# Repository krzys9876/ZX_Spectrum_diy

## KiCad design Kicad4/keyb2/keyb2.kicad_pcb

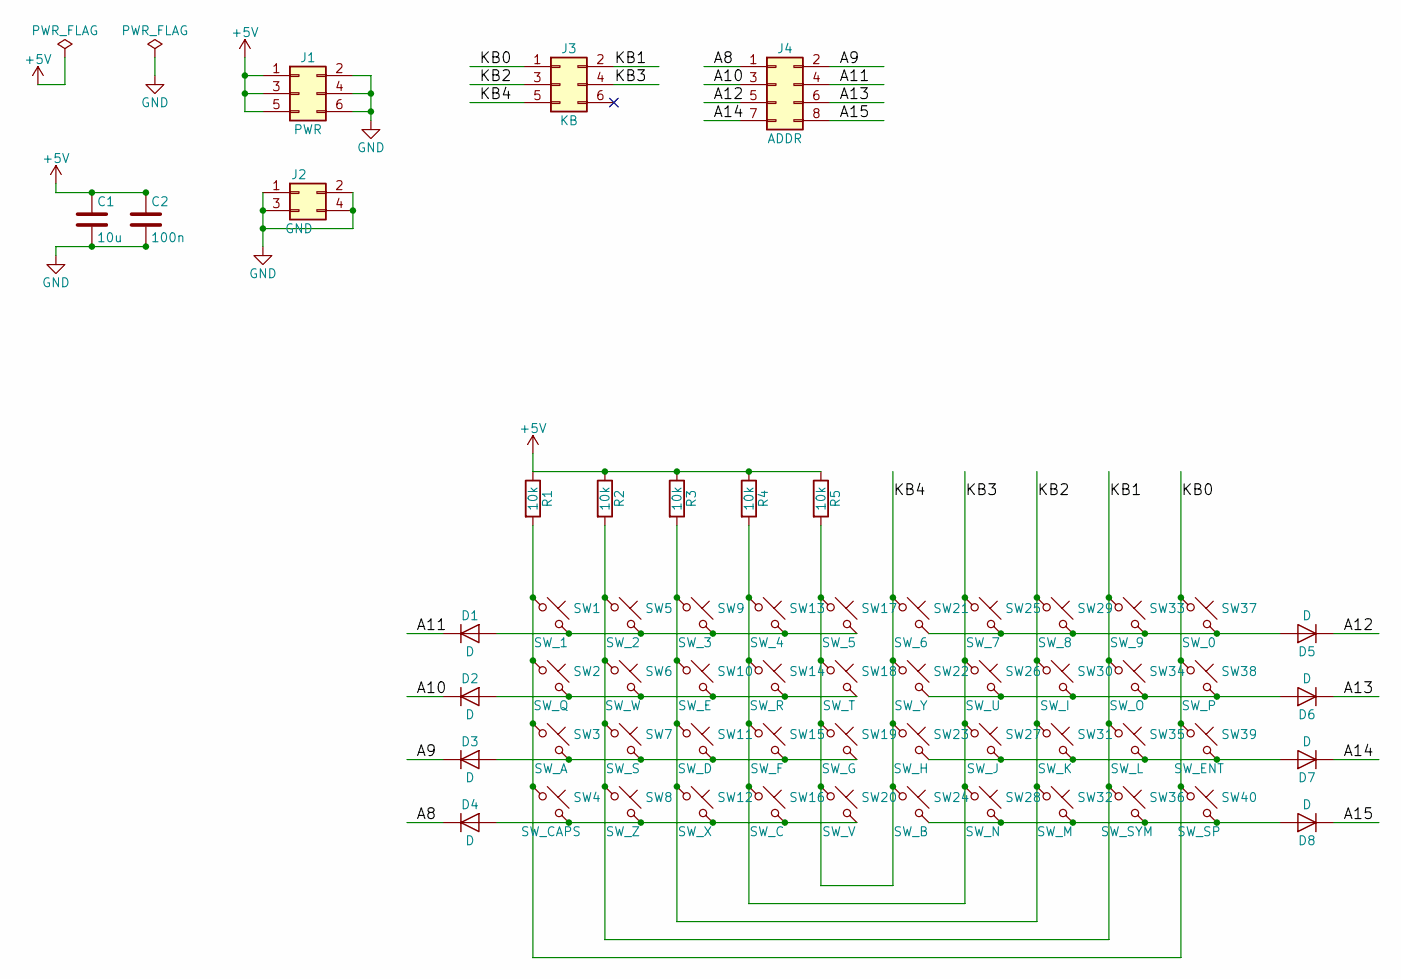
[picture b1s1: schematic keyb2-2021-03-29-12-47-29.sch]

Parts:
C1: 10u; C_1210_HandSoldering
C2: 100n; C_1206_HandSoldering
D1, D2, D3, D4, D5, D6, D7, D8: D; R_0805_HandSoldering
J1: PWR; Pin_Header_Straight_2x03_Pitch2.54mm_SMD
J2: GND; Pin_Header_Straight_2x02_Pitch2.54mm_SMD
J3: KB; Pin_Header_Straight_2x03_Pitch2.54mm_SMD
J4: ADDR; Pin_Header_Straight_2x04_Pitch2.54mm_SMD
R1, R2, R3, R4, R5: 10k; R_0805_HandSoldering
SW1: SW_1; SW_SPST_EVQQ2
SW2: SW_Q; SW_SPST_EVQQ2
SW3: SW_A; SW_SPST_EVQQ2
SW4: SW_CAPS; SW_SPST_EVQQ2
SW5: SW_2; SW_SPST_EVQQ2
SW6: SW_W; SW_SPST_EVQQ2
SW7: SW_S; SW_SPST_EVQQ2
SW8: SW_Z; SW_SPST_EVQQ2
SW9: SW_3; SW_SPST_EVQQ2
SW10: SW_E; SW_SPST_EVQQ2
SW11: SW_D; SW_SPST_EVQQ2
SW12: SW_X; SW_SPST_EVQQ2
SW13: SW_4; SW_SPST_EVQQ2
SW14: SW_R; SW_SPST_EVQQ2
SW15: SW_F; SW_SPST_EVQQ2
SW16: SW_C; SW_SPST_EVQQ2
SW17: SW_5; SW_SPST_EVQQ2
SW18: SW_T; SW_SPST_EVQQ2
SW19: SW_G; SW_SPST_EVQQ2
SW20: SW_V; SW_SPST_EVQQ2
SW21: SW_6; SW_SPST_EVQQ2
SW22: SW_Y; SW_SPST_EVQQ2
SW23: SW_H; SW_SPST_EVQQ2
SW24: SW_B; SW_SPST_EVQQ2
SW25: SW_7; SW_SPST_EVQQ2
SW26: SW_U; SW_SPST_EVQQ2
SW27: SW_J; SW_SPST_EVQQ2
SW28: SW_N; SW_SPST_EVQQ2
SW29: SW_8; SW_SPST_EVQQ2
SW30: SW_I; SW_SPST_EVQQ2
SW31: SW_K; SW_SPST_EVQQ2
SW32: SW_M; SW_SPST_EVQQ2
SW33: SW_9; SW_SPST_EVQQ2
SW34: SW_O; SW_SPST_EVQQ2
SW35: SW_L; SW_SPST_EVQQ2
SW36: SW_SYM; SW_SPST_EVQQ2
SW37: SW_0; SW_SPST_EVQQ2
SW38: SW_P; SW_SPST_EVQQ2
SW39: SW_ENT; SW_SPST_EVQQ2
SW40: SW_SP; SW_SPST_EVQQ2

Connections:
+5V: C1.1, C2.1, J1.1, J1.3, J1.5, R1.1, R2.1, R3.1, R4.1, R5.1
/A8: D4.1 (K), J4.1
/A9: D3.1 (K), J4.2
/A10: D2.1 (K), J4.3
/A11: D1.1 (K), J4.4
/A12: D5.1 (K), J4.5
/A13: D6.1 (K), J4.6
/A14: D7.1 (K), J4.7
/A15: D8.1 (K), J4.8
/KB0: J3.1, R1.2, SW1.1, SW2.1, SW3.1, SW4.1, SW37.1, SW38.1, SW39.1, SW40.1
/KB1: J3.2, R2.2, SW5.1, SW6.1, SW7.1, SW8.1, SW33.1, SW34.1, SW35.1, SW36.1
/KB2: J3.3, R3.2, SW9.1, SW10.1, SW11.1, SW12.1, SW29.1, SW30.1, SW31.1, SW32.1
/KB3: J3.4, R4.2, SW13.1, SW14.1, SW15.1, SW16.1, SW25.1, SW26.1, SW27.1, SW28.1
/KB4: J3.5, R5.2, SW17.1, SW18.1, SW19.1, SW20.1, SW21.1, SW22.1, SW23.1, SW24.1
GND: C1.2, C2.2, J1.2, J1.4, J1.6, J2.1, J2.2, J2.3, J2.4
unnamed: D1.2 (A), SW1.2, SW5.2, SW9.2, SW13.2, SW17.2
unnamed: D2.2 (A), SW2.2, SW6.2, SW10.2, SW14.2, SW18.2
unnamed: D3.2 (A), SW3.2, SW7.2, SW11.2, SW15.2, SW19.2
unnamed: D4.2 (A), SW4.2, SW8.2, SW12.2, SW16.2, SW20.2
unnamed: D5.2 (A), SW21.2, SW25.2, SW29.2, SW33.2, SW37.2
unnamed: D6.2 (A), SW22.2, SW26.2, SW30.2, SW34.2, SW38.2
unnamed: D7.2 (A), SW23.2, SW27.2, SW31.2, SW35.2, SW39.2
unnamed: D8.2 (A), SW24.2, SW28.2, SW32.2, SW36.2, SW40.2

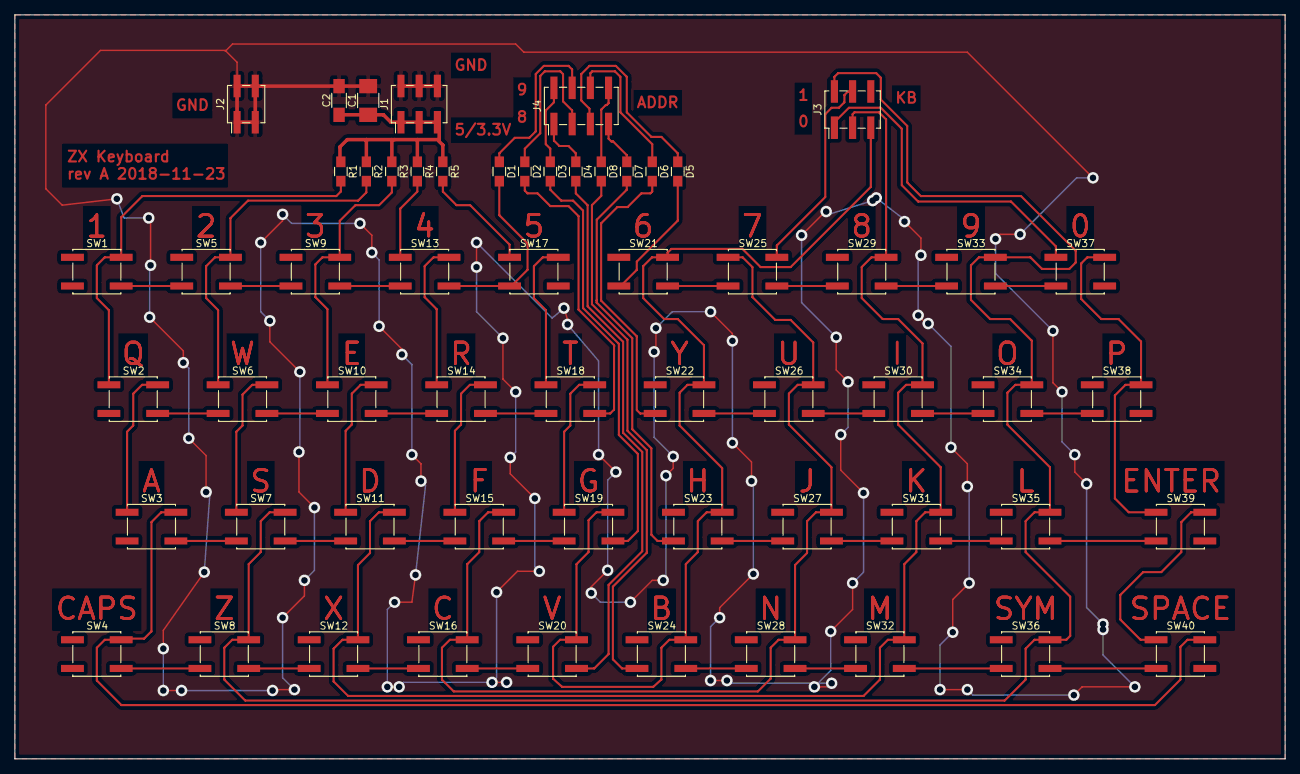
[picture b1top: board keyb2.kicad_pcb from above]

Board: 2 copper layers, 177.2 x 103.8 mm, 59 parts (0 on the bottom side), 23 nets.

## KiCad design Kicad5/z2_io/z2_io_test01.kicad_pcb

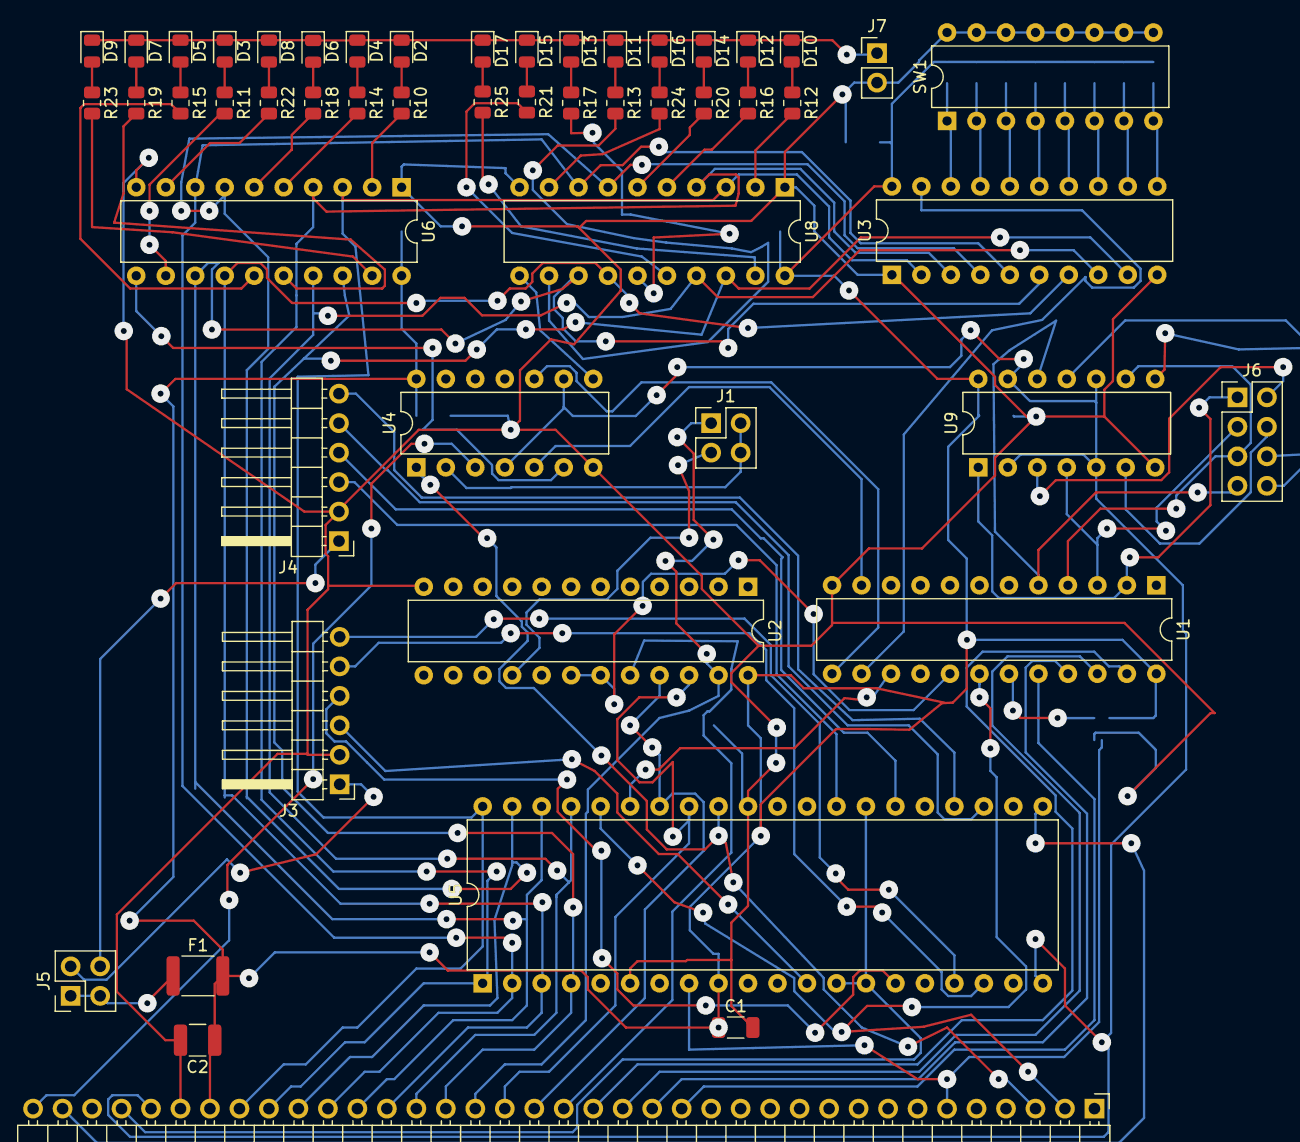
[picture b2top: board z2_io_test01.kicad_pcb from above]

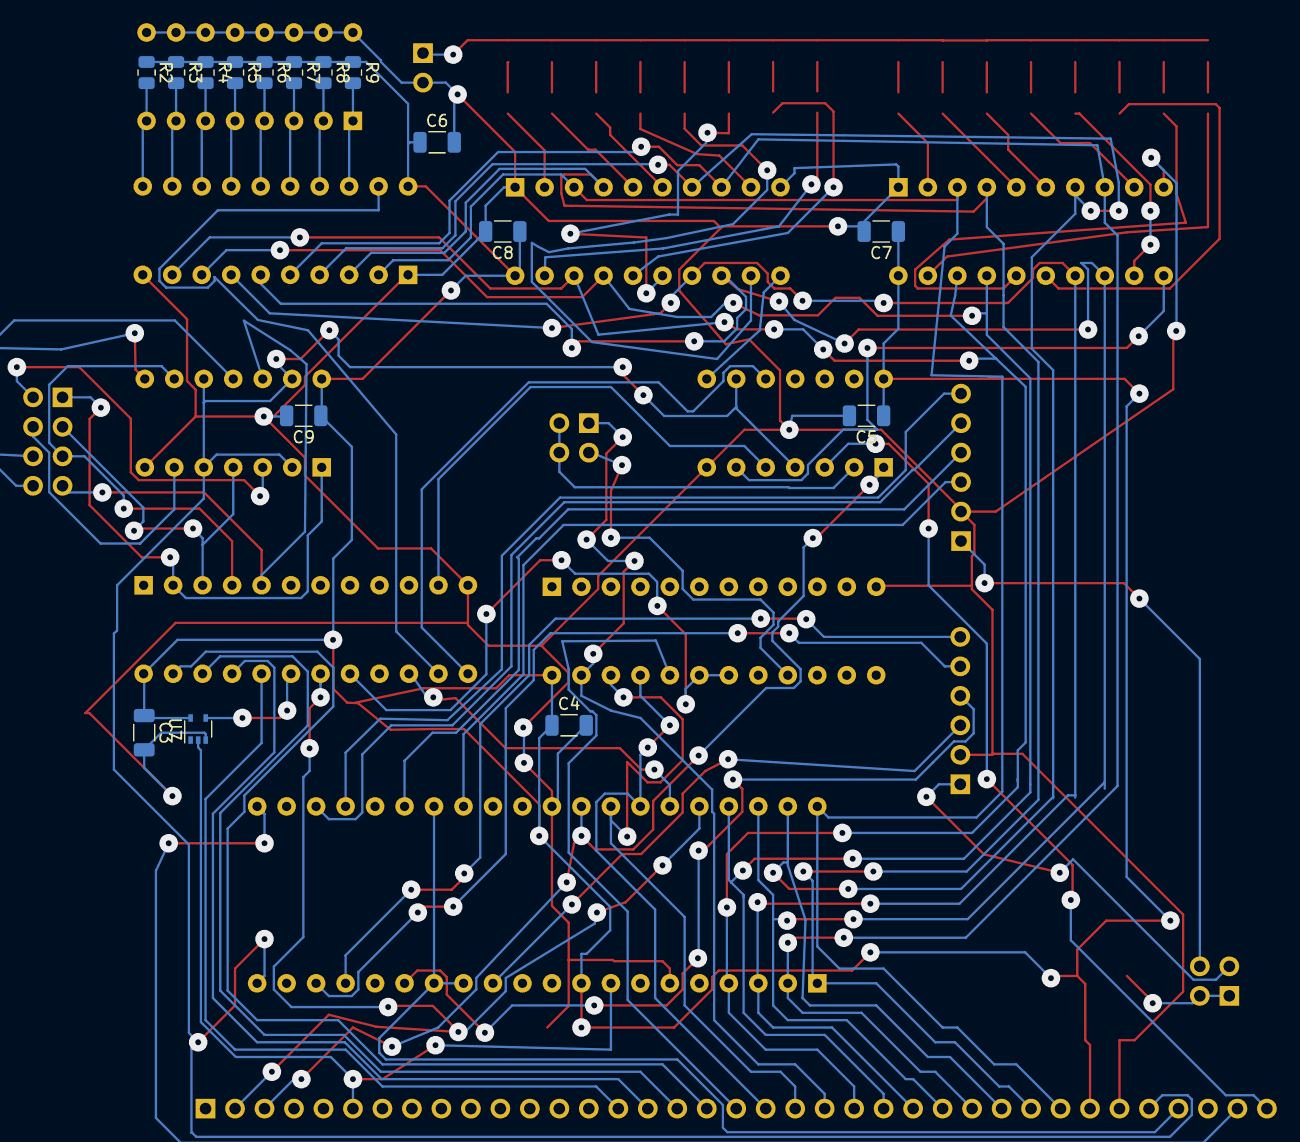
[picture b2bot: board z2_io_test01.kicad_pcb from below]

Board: 2 copper layers, 67 parts (16 on the bottom side), 95 nets.

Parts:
C1, C3, C4, C5, C6, C7, C8, C9: 100n; C_1206_3216Metric
C2: 10u; C_1210_3225Metric
D2, D3, D4, D5, D6, D7, D8, D9, D10, D11, D12, D13, D14, D15, D16, D17: LED; D_0805_2012Metric
F1: Fuse; Fuse_1812_4532Metric
J1: KB_SEL; PinHeader_2x02_P2.54mm_Vertical
J2: CONN; PinHeader_1x37_P2.54mm_Horizontal
J3: UART_A; PinHeader_1x06_P2.54mm_Horizontal
J4: UART_B; PinHeader_1x06_P2.54mm_Horizontal
J5: PW_SEL; PinHeader_2x02_P2.54mm_Vertical
J6: CONN_OUT; PinHeader_2x04_P2.54mm_Vertical
J7: LED_EN; PinHeader_1x02_P2.54mm_Vertical
R2, R3, R4, R5, R6, R7, R8, R9, R10, R11, R12, R13, R14, R15, R16, R17, R18, R19, R20, R21, R22, R23, R24, R25: R; R_0805_2012Metric
SW1: DIP_SW_C; DIP-16_W7.62mm
U1, U2: 74LS154; DIP-24_W7.62mm
U3: 74HC245; DIP-20_W7.62mm
U4, U9: 74LS32; DIP-14_W7.62mm
U5: Z8440; DIP-40_W15.24mm
U6, U8: 74HC374; DIP-20_W7.62mm
U7: 74LVC1G14; SOT-353_SC-70-5

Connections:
/1x_PORT_CK: J6.2, U9.3
/2x_PORT_CK: J6.4, U9.6
/3x_PORT_CK: J6.6, U9.8
/4x_PORT_CK: J6.8, U9.11
/5V: C1.1, C2.1, C3.1, C4.1, C5.1, C6.1, C7.1, C8.1, C9.1, F1.2, J2.31, R2.1, R3.1, R4.1, R5.1, R6.1, R7.1, R8.1, R9.1, U1.24, U2.24, U3.20, U4.14, U5.9, U6.20, U7.5, U8.20, U9.14
/5V_UART_A: J3.1, J5.2
/5V_UART_B: J4.1, J5.4
/A0: J1.1, J2.22, U2.23
/A1: J2.21, U2.22, U5.33
/A2: J2.20, U2.21, U5.34
/A3: J2.19, U2.20
/A4: J2.18, U1.23
/A5: J2.17, U1.22
/A6: J2.16, U1.21
/A7: J2.15, U1.20
/CLK: J2.33, U4.4, U4.9, U5.20, U9.2, U9.5, U9.10, U9.13
/CLK2: J2.34, U5.13, U5.14, U5.27
/D0: J2.30, U3.2, U5.40, U6.3, U8.3
/D1: J2.29, U3.3, U5.1, U6.4, U8.4
/D2: J2.28, U3.4, U5.39, U6.7, U8.7
/D3: J2.27, U3.5, U5.2, U6.8, U8.8
/D4: J2.26, U3.6, U5.38, U6.13, U8.13
/D5: J2.25, U3.7, U5.3, U6.14, U8.14
/D6: J2.24, U3.8, U5.37, U6.17, U8.17
/D7: J2.23, U3.9, U5.4, U6.18, U8.18
/GND: C1.2, C2.2, C3.2, C4.2, C5.2, C6.2, C7.2, C8.2, C9.2, J2.32, J3.2, J4.2, J7.2, SW1.9, SW1.10, SW1.11, SW1.12, SW1.13, SW1.14, SW1.15, SW1.16, U1.12, U2.12, U3.1, U3.10, U4.7, U5.6, U5.31, U6.1, U6.10, U7.3, U8.1, U8.10, U9.7
/M1: U1.19, U7.4
/RX_A: J3.4, U5.15
/RX_B: J4.4, U5.26
/TX_A: J3.3, U5.12
/TX_B: J4.3, U5.28
/~1x_PORT: J6.1, U1.2, U9.1
/~2x_PORT: J6.3, U1.3, U9.4
/~3x_PORT: J6.5, U1.4, U9.9
/~4x_PORT: J6.7, U1.5, U9.12
/~Ax_PORT: U1.11, U4.5
/~Bx_PORT: U1.13, U4.10
/~CTS_A: J3.6, U5.17
/~CTS_B: J4.6, U5.24
/~Cx_PORT: U1.14, U3.19
/~Dx_PORT: U1.15, U5.35
/~FE_PORT: J1.3, U2.16
/~Fx_PORT: U1.17, U2.18, U2.19
/~IORQ: J2.2, U1.18, U5.36
/~KBEN: J2.37, U4.3
/~M1: J2.6, U5.8, U7.2
/~RD: J2.3, U4.1, U5.32
/~RESET: J2.36, U5.21
/~RTS_A: J3.5, U5.18
/~RTS_B: J4.5, U5.23
unnamed: D2.2, R10.1
unnamed: D3.2, R11.1
unnamed: D4.2, R14.1
unnamed: D5.2, R15.1
unnamed: D6.2, R18.1
unnamed: D7.2, R19.1
unnamed: D8.2, R22.1
unnamed: D9.2, R23.1
unnamed: D2.1, D3.1, D4.1, D5.1, D6.1, D7.1, D8.1, D9.1, D10.1, D11.1, D12.1, D13.1, D14.1, D15.1, D16.1, D17.1, J7.1
unnamed: D10.2, R12.1
unnamed: D11.2, R13.1
unnamed: D12.2, R16.1
unnamed: D13.2, R17.1
unnamed: D14.2, R20.1
unnamed: D15.2, R21.1
unnamed: D16.2, R24.1
unnamed: D17.2, R25.1
unnamed: F1.1, J5.1, J5.3
unnamed: J1.2, J1.4, U4.2
unnamed: R2.2, SW1.8, U3.11
unnamed: R3.2, SW1.7, U3.12
unnamed: R4.2, SW1.6, U3.13
unnamed: R5.2, SW1.5, U3.14
unnamed: R6.2, SW1.4, U3.15
unnamed: R7.2, SW1.3, U3.16
unnamed: R8.2, SW1.2, U3.17
unnamed: R9.2, SW1.1, U3.18
unnamed: R10.2, U6.2
unnamed: R11.2, U6.12
unnamed: R12.2, U8.2
unnamed: R13.2, U8.12
unnamed: R14.2, U6.5
unnamed: R15.2, U6.15
unnamed: R16.2, U8.5
unnamed: R17.2, U8.15
unnamed: R18.2, U6.6
unnamed: R19.2, U6.16
unnamed: R20.2, U8.6
unnamed: R21.2, U8.16
unnamed: R22.2, U6.9
unnamed: R23.2, U6.19
unnamed: R24.2, U8.9
unnamed: R25.2, U8.19
unnamed: U4.6, U6.11
unnamed: U4.8, U8.11

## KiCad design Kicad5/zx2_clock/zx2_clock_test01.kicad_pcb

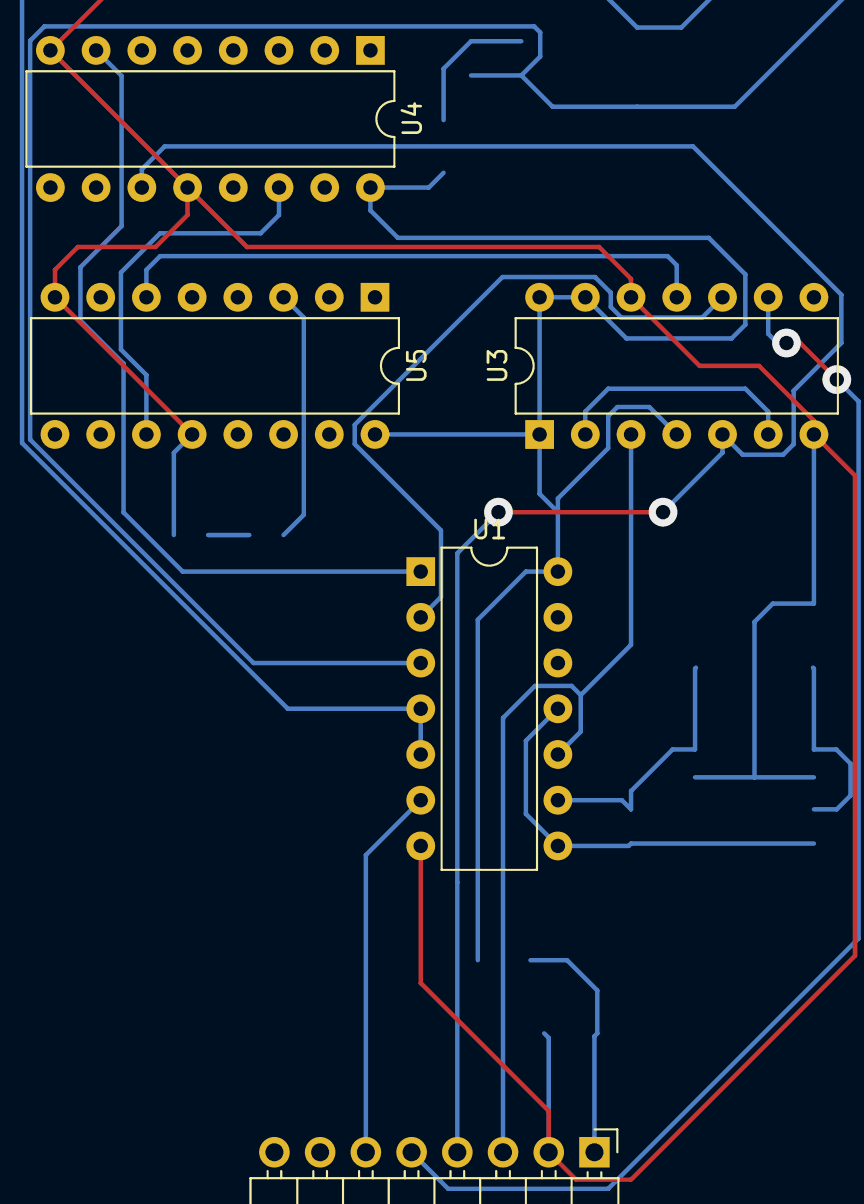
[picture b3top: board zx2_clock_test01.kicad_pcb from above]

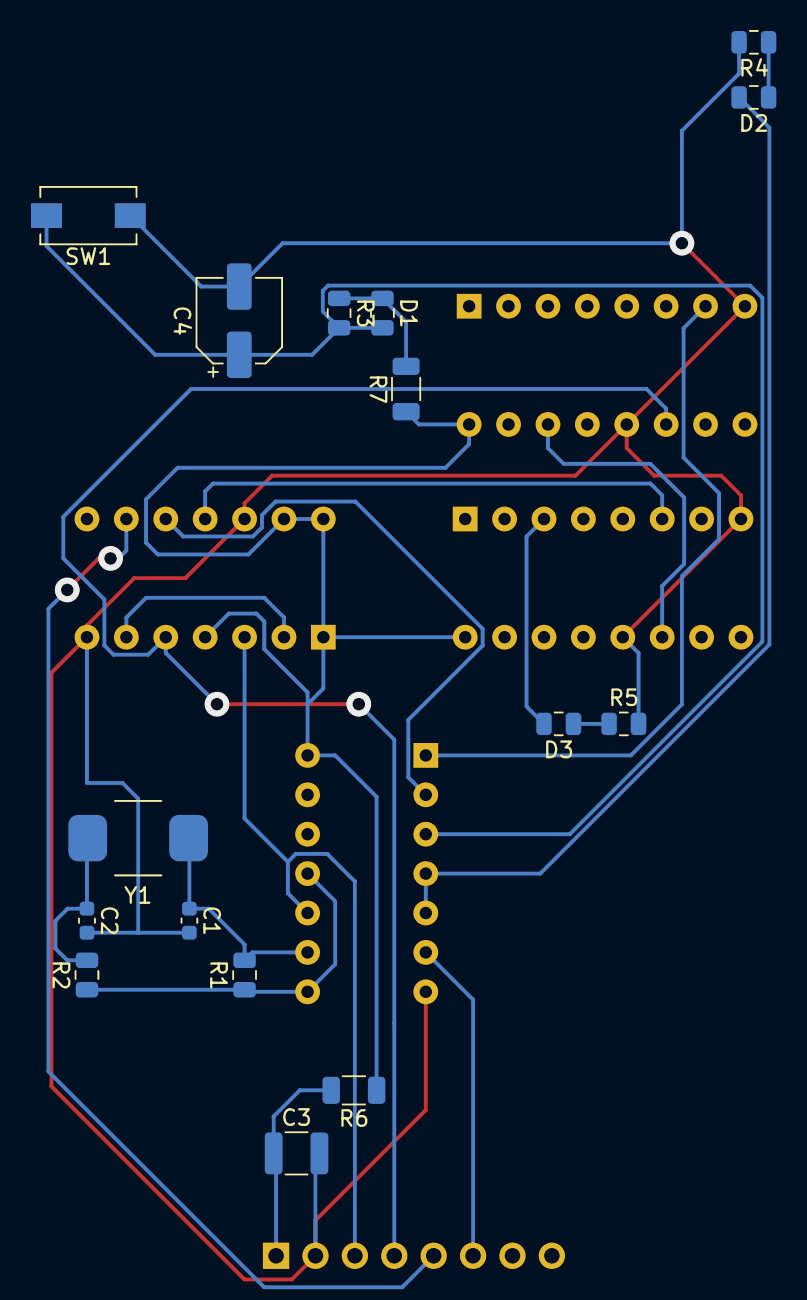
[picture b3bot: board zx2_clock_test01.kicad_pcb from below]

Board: 2 copper layers, 21 parts (16 on the bottom side), 19 nets.

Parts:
C1, C2: 22p; C_0603_1608Metric
C3: CP; C_1210_3225Metric
C4: 50u; CP_Elec_5x3
D1: D; C_0805_2012Metric
D2, D3: LED; C_0805_2012Metric
J1: CONN_AUX; PinHeader_1x08_P2.54mm_Horizontal
R1: 1M; C_0805_2012Metric
R2: R; C_0805_2012Metric
R3: 100k; C_0805_2012Metric
R4, R5: 2.2k; C_0805_2012Metric
R6, R7: 0R; R_1206_3216Metric
SW1: SW_MEC_5G; SW_SPST_EVQPE1
U1: 74HC14; DIP-14_W7.62mm
U3: 74HC74; DIP-14_W7.62mm
U4, U5: CD4060; DIP-16_W7.62mm
Y1: 3.6768MHz; Crystal_SMD_TXC_AX_8045-2Pin_8.0x4.5mm

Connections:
+5V: C3.1, D1.1, J1.1, R3.1, R6.1, R6.2, R7.1, R7.2, U1.14, U3.1, U3.4, U3.13, U3.14, U4.16, U5.16
/CLK: J1.3, U1.10, U3.3
/CLK2: J1.4, U3.5, U4.11
/~INT: J1.5, U3.9
/~RESET: J1.6, U1.6
GND: C1.2, C2.2, C3.2, C4.2, J1.2, R4.2, R5.2, SW1.1, U1.7, U3.7, U3.12, U4.8, U4.12, U5.8, U5.12
unnamed: C1.1, R1.2, U1.9, Y1.1
unnamed: C2.1, R2.2, Y1.2
unnamed: C4.1, D1.2, R3.2, SW1.2, U1.3
unnamed: D2.1, R4.1
unnamed: D2.2, U1.4, U1.5
unnamed: D3.1, R5.1
unnamed: D3.2, U5.3
unnamed: R1.1, R2.1, U1.8, U1.11
unnamed: U1.1, U4.7
unnamed: U1.2, U3.10
unnamed: U3.2, U3.6
unnamed: U3.11, U5.6
unnamed: U4.14, U5.11

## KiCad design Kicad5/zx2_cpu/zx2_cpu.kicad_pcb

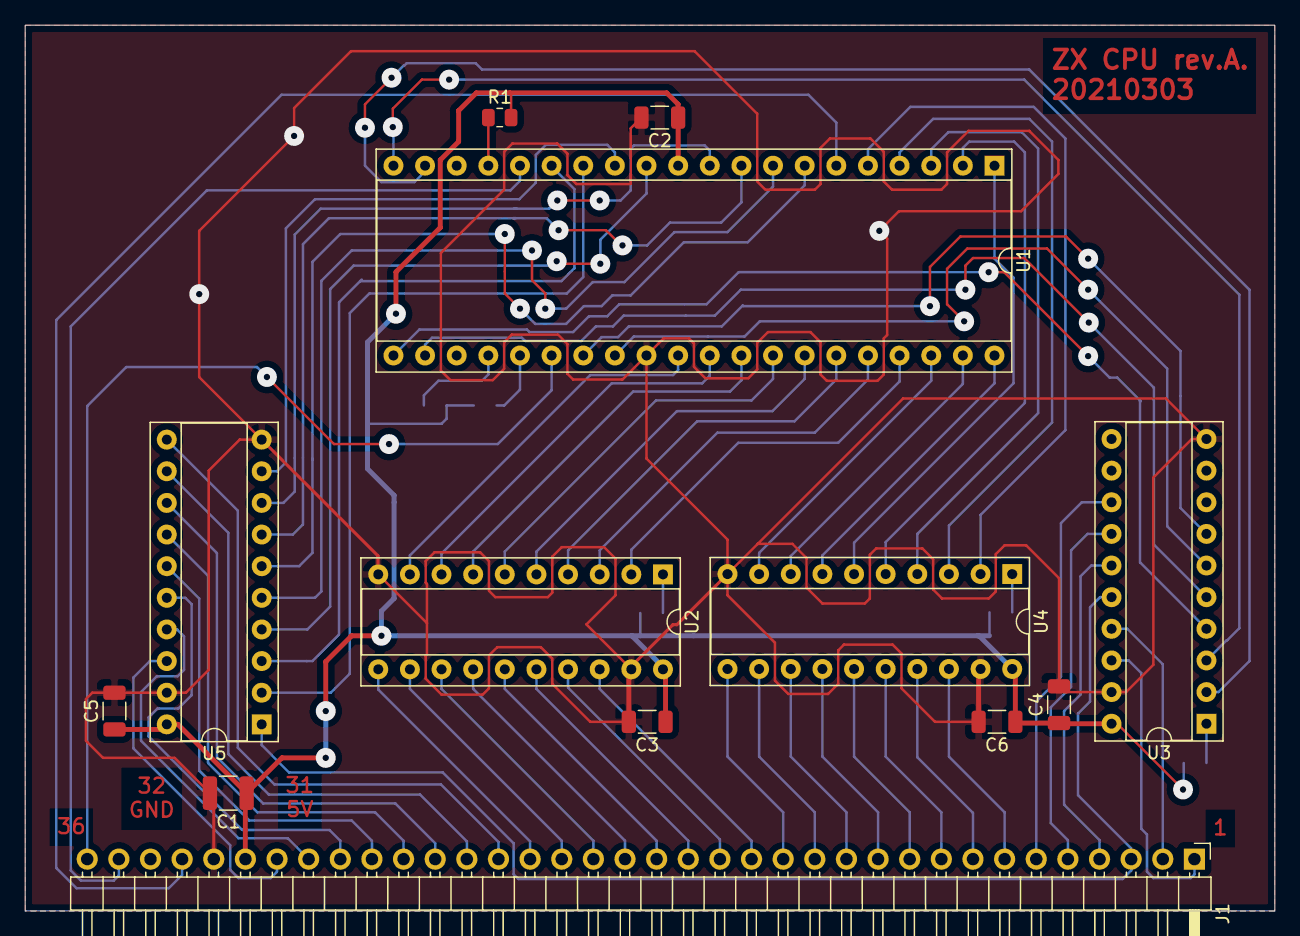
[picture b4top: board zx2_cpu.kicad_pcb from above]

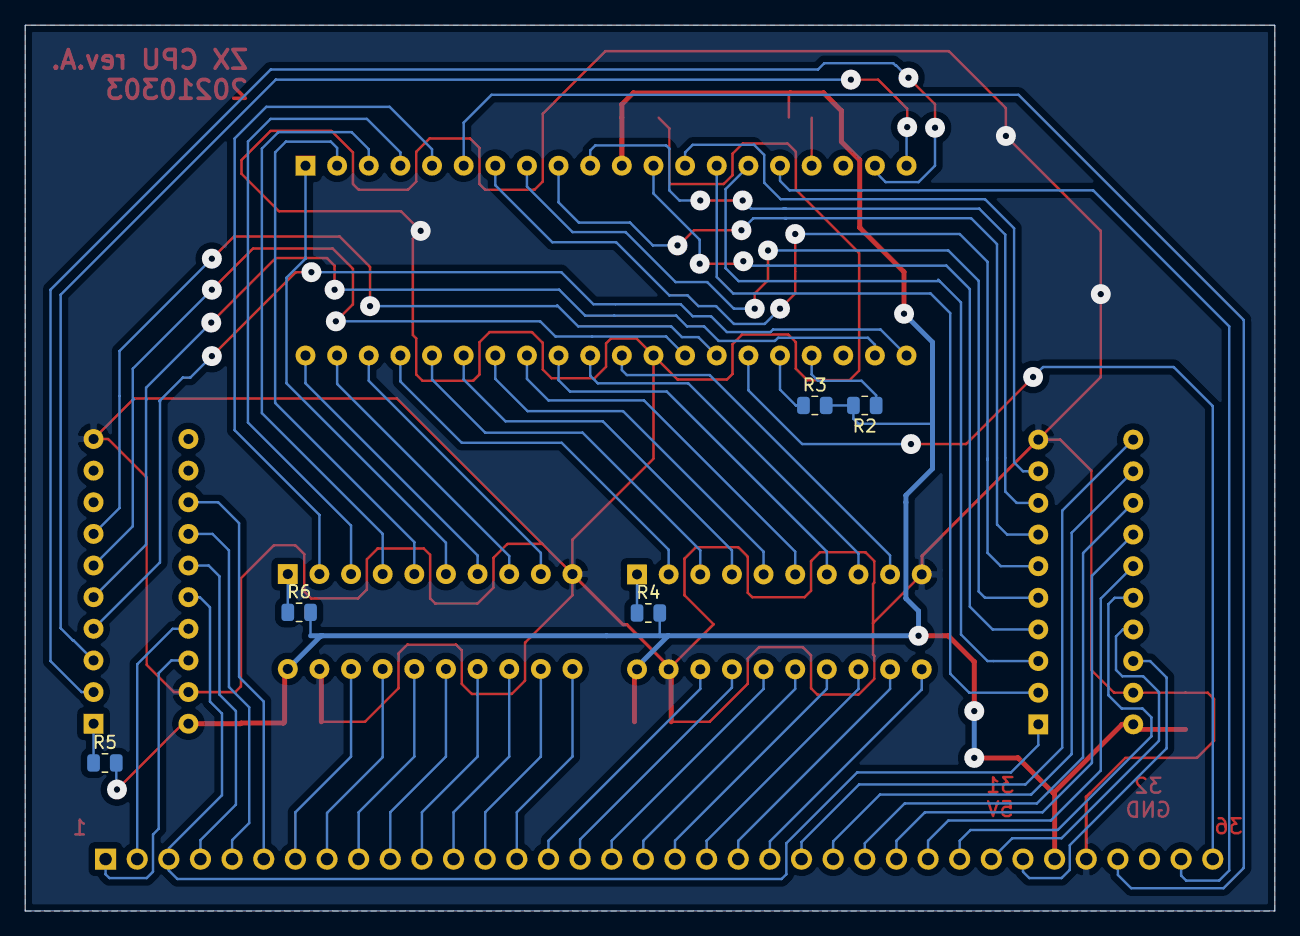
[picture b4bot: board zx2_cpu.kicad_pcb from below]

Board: 2 copper layers, 100.3 x 71.1 mm, 18 parts (5 on the bottom side), 71 nets.

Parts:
C1: CP; C_1210_3225Metric
C2, C3, C4, C5, C6: 100n; C_1206_3216Metric
J1: Conn_01x36; PinHeader_1x36_P2.54mm_Horizontal
R1, R2, R3, R4, R5, R6: R; R_0805_2012Metric
U1: Z80CPU; DIP-40_W15.24mm_Socket
U2, U3, U4, U5: 74HC245; DIP-20_W7.62mm_Socket

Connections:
/5V: C1.1, C2.1, C3.1, C4.1, C5.1, C6.1, J1.31, R1.2, R2.2, R3.2, R4.2, R5.2, R6.2, U1.11, U2.20, U3.20, U4.20, U5.20
/A0: J1.22, U2.11
/A0CPU: U1.30, U2.9
/A1: J1.21, U2.12
/A1CPU: U1.31, U2.8
/A2: J1.20, U2.13
/A2CPU: U1.32, U2.7
/A3: J1.19, U2.14
/A3CPU: U1.33, U2.6
/A4: J1.18, U2.15
/A4CPU: U1.34, U2.5
/A5: J1.17, U2.16
/A5CPU: U1.35, U2.4
/A6: J1.16, U2.17
/A6CPU: U1.36, U2.3
/A7: J1.15, U2.18
/A7CPU: U1.37, U2.2
/A8: J1.14, U4.11
/A8CPU: U1.38, U4.9
/A9: J1.13, U4.12
/A9CPU: U1.39, U4.8
/A10: J1.12, U4.13
/A10CPU: U1.40, U4.7
/A11: J1.11, U4.14
/A11CPU: U1.1, U4.6
/A12: J1.10, U4.15
/A12CPU: U1.2, U4.5
/A13: J1.9, U4.16
/A13CPU: U1.3, U4.4
/A14: J1.8, U4.17
/A14CPU: U1.4, U4.3
/A15: J1.7, U4.18
/A15CPU: U1.5, U4.2
/CLK: J1.33, U1.6
/D0: J1.30, U5.18
/D0CPU: U1.14, U5.2
/D1: J1.29, U5.17
/D1CPU: U1.15, U5.3
/D2: J1.28, U5.16
/D2CPU: U1.12, U5.4
/D3: J1.27, U5.15
/D3CPU: U1.8, U5.5
/D4: J1.26, U5.14
/D4CPU: U1.7, U5.6
/D5: J1.25, U5.13
/D5CPU: U1.9, U5.7
/D6: J1.24, U5.12
/D6CPU: U1.10, U5.8
/D7: J1.23, U5.11
/D7CPU: U1.13, U5.9
/GND: C1.2, C2.2, C3.2, C4.2, C5.2, C6.2, J1.32, U1.29, U2.10, U2.19, U3.10, U3.19, U4.10, U4.19, U5.10, U5.19
/~INT: J1.35, U1.16
/~IORQ: J1.2, U3.17
/~IORQCPU: U1.20, U3.3
/~M1: J1.6, U3.13
/~M1CPU: U1.27, U3.7
/~MREQ: J1.1, U3.18
/~MREQCPU: U1.19, U3.2
/~RD: J1.3, U3.16, U5.1
/~RDCPU: U1.21, U3.4
/~RESET: J1.36, U1.26
/~RFSH: J1.5, U3.14
/~RFSHCPU: U1.28, U3.6
/~WR: J1.4, U3.15
/~WRCPU: U1.22, U3.5
unnamed: R1.1, U1.17
unnamed: R2.1, U1.24
unnamed: R3.1, U1.25
unnamed: R4.1, U2.1
unnamed: R5.1, U3.1
unnamed: R6.1, U4.1

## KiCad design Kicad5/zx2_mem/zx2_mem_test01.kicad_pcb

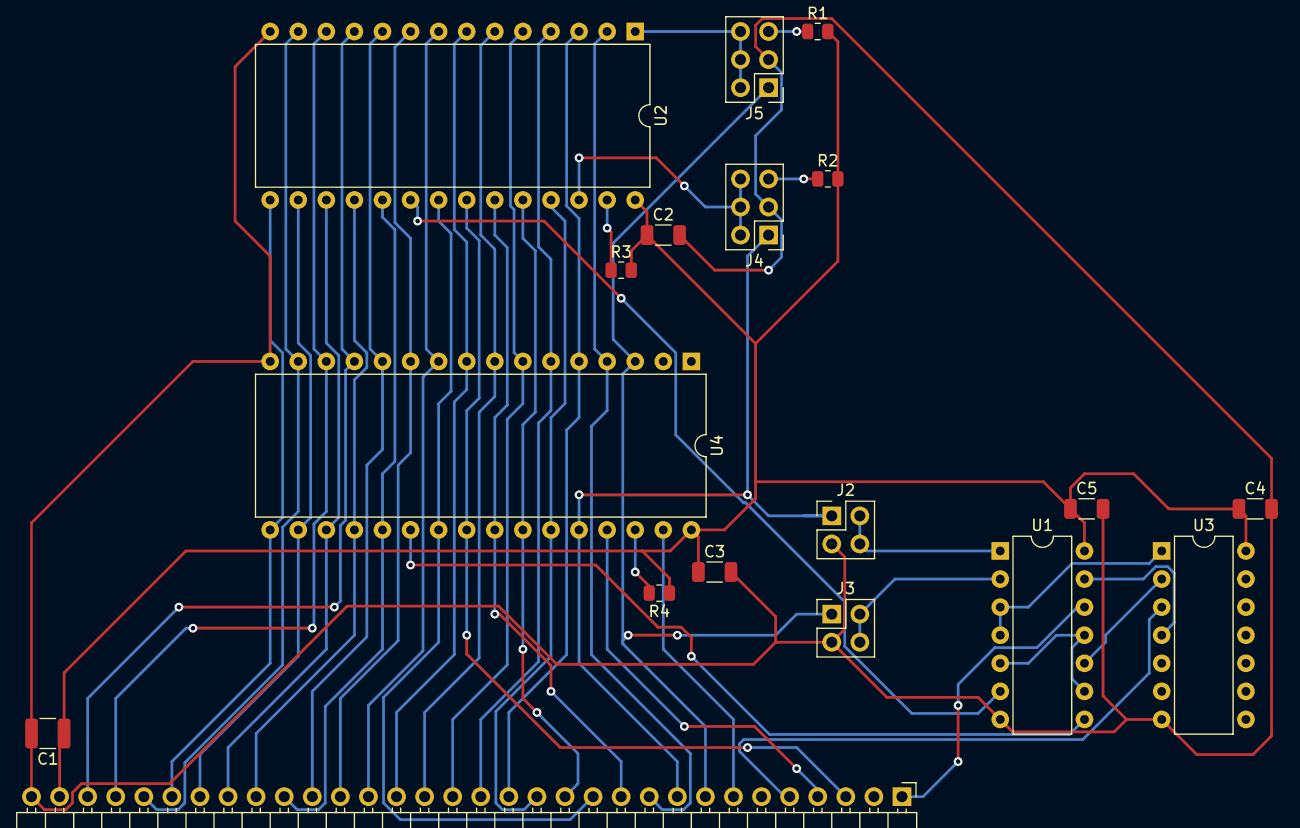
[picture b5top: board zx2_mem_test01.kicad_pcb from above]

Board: 2 copper layers, 18 parts (0 on the bottom side), 44 nets.

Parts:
C1: CP; C_1210_3225Metric
C2, C3, C4, C5: 100n; C_1206_3216Metric
J1: Conn_01x32; PinHeader_1x32_P2.54mm_Horizontal
J2: A13_DECODER; PinHeader_2x02_P2.54mm_Vertical
J3: A14_DECODER; PinHeader_2x02_P2.54mm_Vertical
J4: A13_ROM; PinHeader_2x03_P2.54mm_Vertical
J5: A14_ROM; PinHeader_2x03_P2.54mm_Vertical
R1, R2, R3, R4: R; R_0805_2012Metric
U1, U3: 74LS32; DIP-14_W7.62mm
U2: 28C256; DIP-28_W15.24mm
U4: AS6C1008-55PCN; DIP-32_W15.24mm

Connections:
/5V: C1.1, C2.1, C3.1, C4.1, C5.1, J1.31, R1.2, R2.2, R3.2, R4.1, U1.14, U2.28, U3.14, U4.32
/A0: J1.22, U2.10, U4.12
/A1: J1.21, U2.9, U4.11
/A2: J1.20, U2.8, U4.10
/A3: J1.19, U2.7, U4.9
/A4: J1.18, U2.6, U4.8
/A5: J1.17, U2.5, U4.7
/A6: J1.16, U2.4, U4.6
/A7: J1.15, U2.3, U4.5
/A8: J1.14, U2.25, U4.27
/A9: J1.13, U2.24, U4.26
/A10: J1.12, U2.21, U4.23
/A11: J1.11, U2.23, U4.25
/A12: J1.10, U2.2, U4.4
/A13: J1.9, J2.1, J4.1, U4.28
/A13DEC: J2.2, J2.4, U1.1
/A13ROM: J4.2, J4.4, J4.6, U2.26
/A14: J1.8, J3.1, J5.1, U4.3
/A14DEC: J3.2, J3.4, U1.2
/A14ROM: J5.2, J5.4, J5.6, U2.1
/A15: J1.7, U4.31
/D0: J1.30, U2.11, U4.13
/D1: J1.29, U2.12, U4.14
/D2: J1.28, U2.13, U4.15
/D3: J1.27, U2.15, U4.17
/D4: J1.26, U2.16, U4.18
/D5: J1.25, U2.17, U4.19
/D6: J1.24, U2.18, U4.20
/D7: J1.23, U2.19, U4.21
/GND: C1.2, C2.2, C3.2, C4.2, C5.2, J1.32, J2.3, J3.3, J4.3, J5.3, U1.7, U2.14, U3.7, U4.16
/~MEM_EN: U1.5, U1.9, U1.11
/~MREQ: J1.1, U1.12
/~RAM_EN: U1.8, U4.22
/~RD: J1.3, U2.22, U4.24
/~RFSH: J1.5, U3.3
/~ROM_EN: U1.6, U2.20
/~ROM_RANGE: U1.3, U1.4, U3.1
/~WR: J1.4, U4.29
unnamed: J4.5, R2.1
unnamed: J5.5, R1.1
unnamed: R3.1, U2.27
unnamed: R4.2, U4.30
unnamed: U1.10, U3.2
unnamed: U1.13, U3.4
